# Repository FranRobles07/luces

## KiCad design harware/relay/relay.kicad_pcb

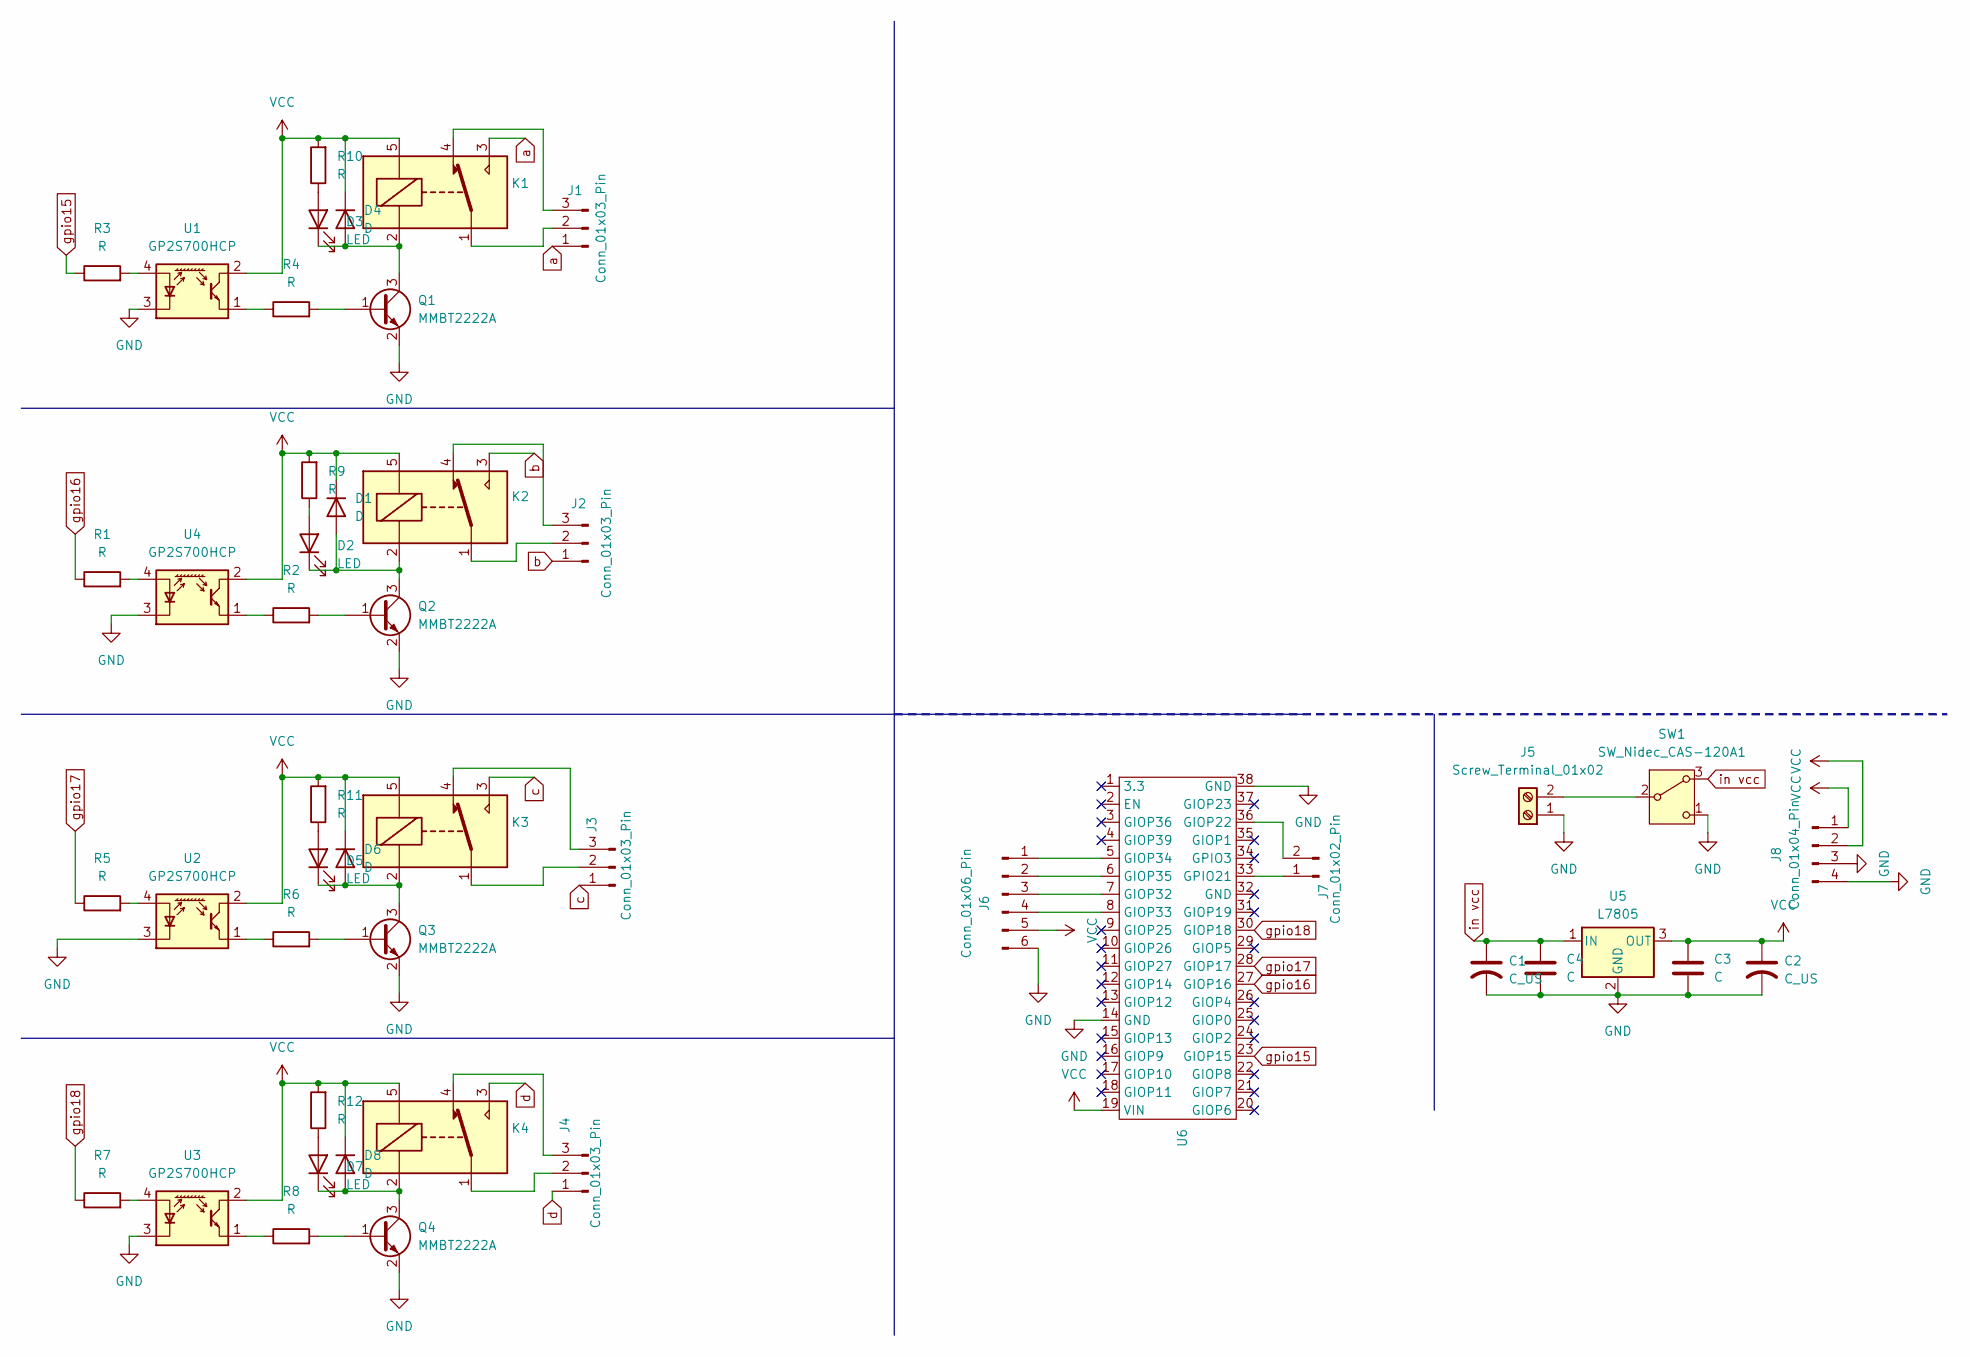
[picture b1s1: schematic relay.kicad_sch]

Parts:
C1, C2: C_US; CAP_ELEC_8x11.5mm
C3, C4: C; CAP_0.1
D1, D4, D6, D8: D; D_0805_2012Metric
D2, D3, D5, D7: LED; LED_0805_2012Metric
J1, J2, J3, J4: Conn_01x03_Pin; TerminalBlock_bornier-3_P5.08mm
J5: Screw_Terminal_01x02; TerminalBlock_bornier-2_P5.08mm
J6: Conn_01x06_Pin; PinHeader_1x06_P2.54mm_Vertical
J7: Conn_01x02_Pin; PinHeader_1x02_P2.54mm_Vertical
J8: Conn_01x04_Pin; PinHeader_1x04_P2.54mm_Vertical
K1, K2, K3, K4: SANYOU_SRD_Form_C; Relay_SPDT_SANYOU_SRD_Series_Form_C
Q1, Q2, Q3, Q4: MMBT2222A; SOT-23
R1, R2, R3, R4, R5, R6, R7, R8, R9, R10, R11, R12: R; R_0805_2012Metric
SW1: SW_Nidec_CAS-120A1; PinHeader_1x03_P2.00mm_Vertical
U1, U2, U3, U4: GP2S700HCP; yokoono
U5: L7805; Converter_DCDC_RECOM_R-78E-0.5_THT
U6: ESP32S_38_PINES

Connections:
GND: C1.2, C2.2, C3.2, C4.2, J5.1, J6.6, J8.3, J8.4, Q1.2 (E), Q2.2 (E), Q3.2 (E), Q4.2 (E), SW1.1 (C), U1.3 (K), U2.3 (K), U3.3 (K), U4.3 (K), U5.2 (GND), U6.14 (GND), U6.38 (GND)
unnamed: D1.2 (A), D2.1 (K), K2.2, Q2.3 (C)
unnamed: D2.2 (A), R9.1
unnamed: D3.2 (A), R10.1
unnamed: D3.1 (K), D4.2 (A), K1.2, Q1.3 (C)
unnamed: D5.2 (A), R11.1
unnamed: D5.1 (K), D6.2 (A), K3.2, Q3.3 (C)
unnamed: D7.2 (A), R12.1
unnamed: D7.1 (K), D8.2 (A), K4.2, Q4.3 (C)
unnamed: J1.2, K1.1
unnamed: J1.3, K1.4
unnamed: J2.2, K2.1
unnamed: J2.3, K2.4
unnamed: J3.2, K3.1
unnamed: J3.3, K3.4
unnamed: J4.2, K4.1
unnamed: J4.3, K4.4
unnamed: J5.2, SW1.2 (B)
unnamed: J6.1, U6.5 (GIOP34)
unnamed: J6.2, U6.6 (GIOP35)
unnamed: J6.3, U6.7 (GIOP32)
unnamed: J6.4, U6.8 (GIOP33)
unnamed: J7.1, U6.33 (GPIO21)
unnamed: J7.2, U6.36 (GIOP22)
unnamed: Q1.1 (B), R4.2
unnamed: Q2.1 (B), R2.2
unnamed: Q3.1 (B), R6.2
unnamed: Q4.1 (B), R8.2
unnamed: R2.1, U4.1
unnamed: R4.1, U1.1
unnamed: R6.1, U2.1
unnamed: R8.1, U3.1
unnamed: R3.2, U1.4 (A)
unnamed: R5.2, U2.4 (A)
unnamed: R7.2, U3.4 (A)
unnamed: R1.2, U4.4 (A)
VCC: C2.1, C3.1, D1.1 (K), D4.1 (K), D6.1 (K), D8.1 (K), J6.5, J8.1, J8.2, K1.5, K2.5, K3.5, K4.5, R9.2, R10.2, R11.2, R12.2, U1.2, U2.2, U3.2, U4.2, U5.3 (OUT), U6.19 (VIN)
a: J1.1, K1.3
b: J2.1, K2.3
c: J3.1, K3.3
d: J4.1, K4.3
gpio15: R3.1, U6.23 (GIOP15)
gpio16: R1.1, U6.27 (GIOP16)
gpio17: R5.1, U6.28 (GIOP17)
gpio18: R7.1, U6.30 (GIOP18)
in vcc: C1.1, C4.1, SW1.3 (A), U5.1 (IN)

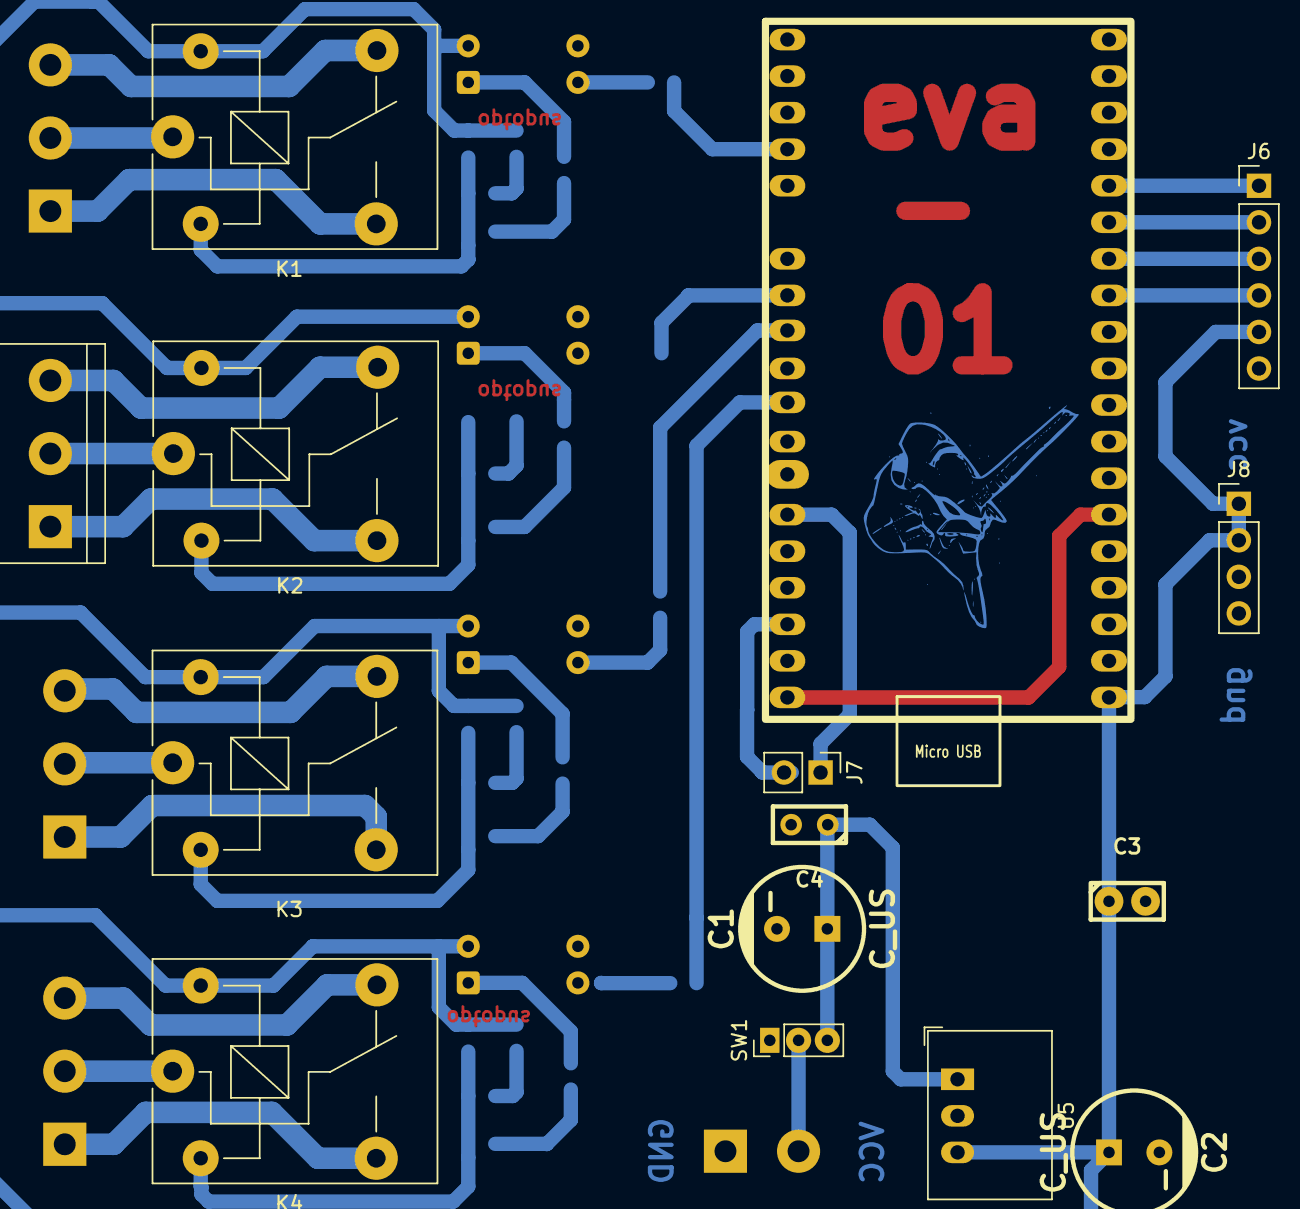
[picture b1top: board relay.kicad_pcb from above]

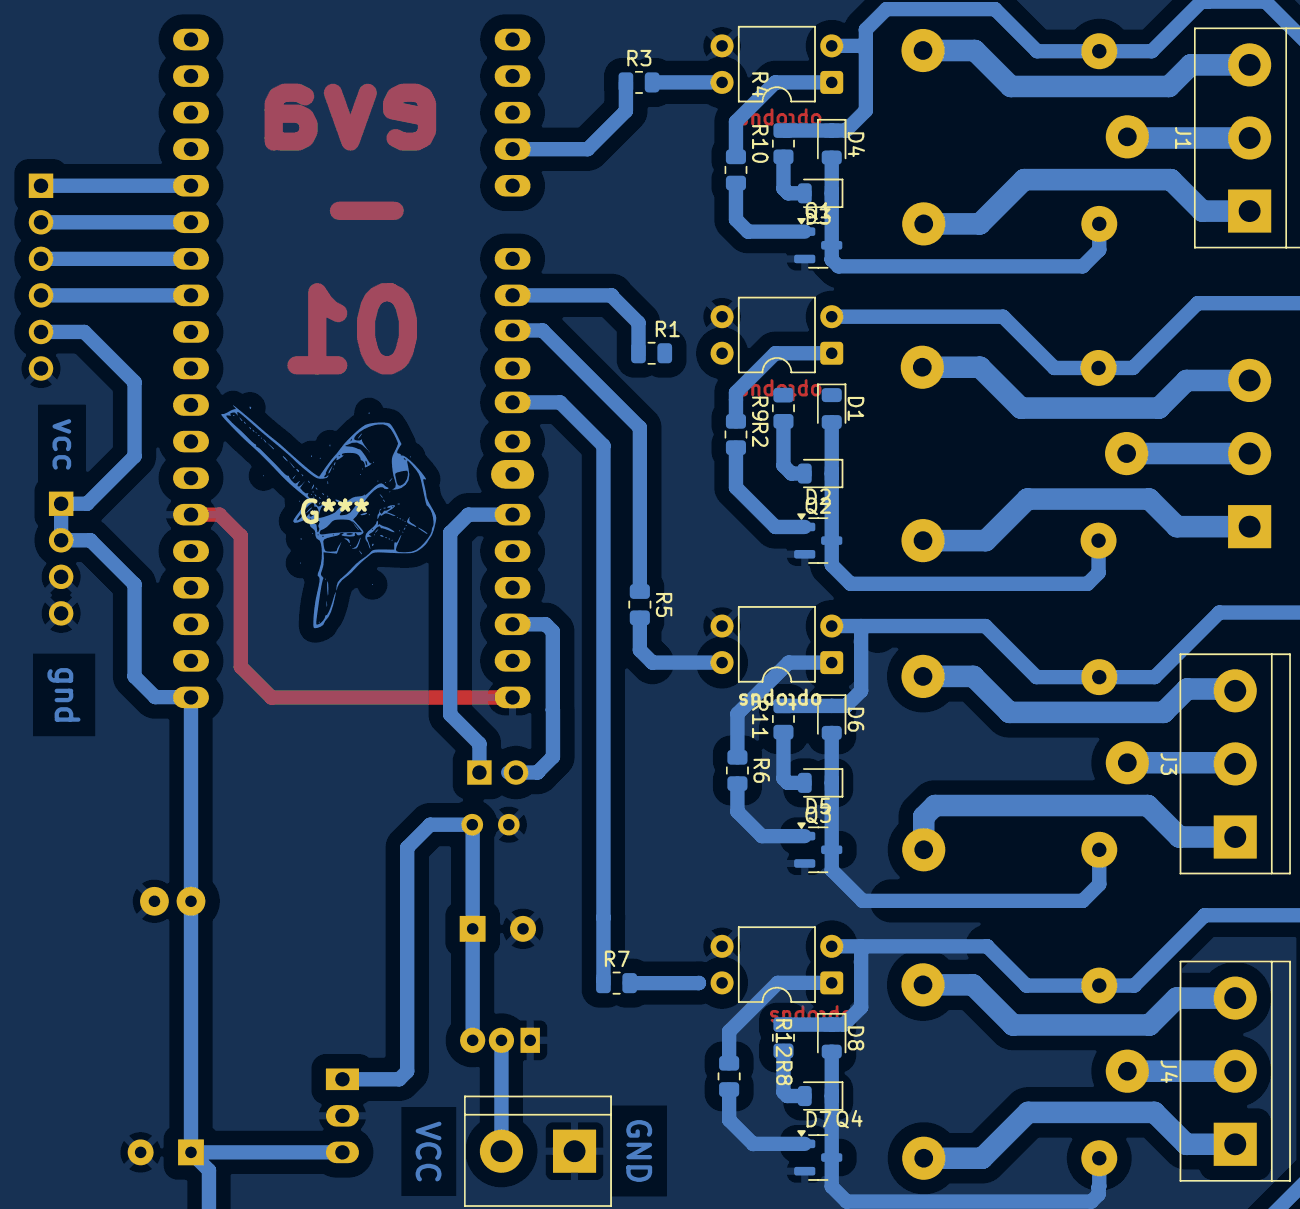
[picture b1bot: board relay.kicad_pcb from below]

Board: 2 copper layers, 47 parts (32 on the bottom side), 46 nets.

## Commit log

2025-07-08 Create relay
